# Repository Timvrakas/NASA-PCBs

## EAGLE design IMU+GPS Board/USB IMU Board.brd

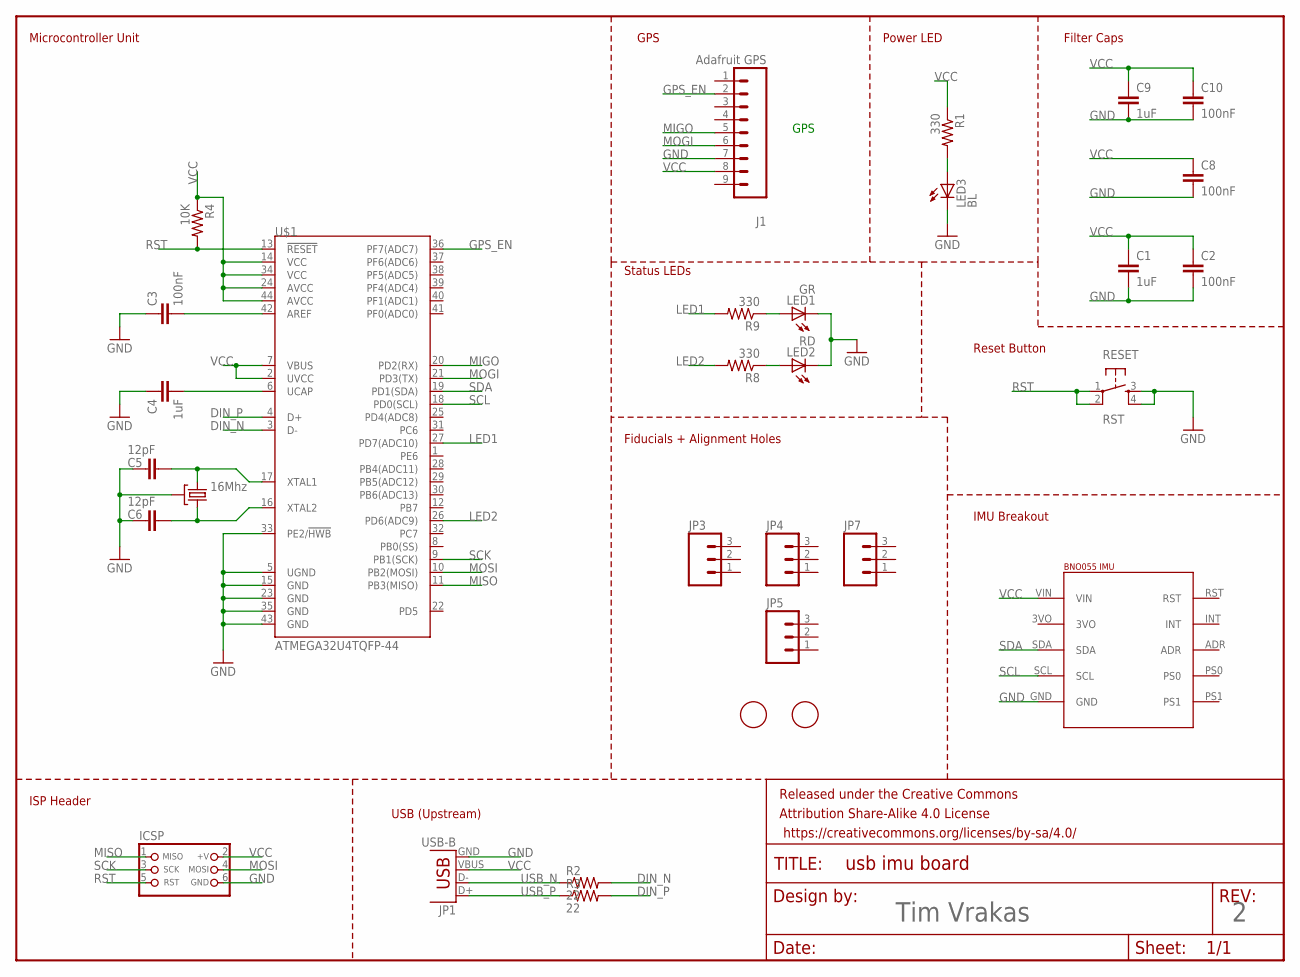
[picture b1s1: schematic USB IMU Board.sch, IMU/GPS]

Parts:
C1, C4, C9: 1uF; 0805
C2, C3, C8, C10: 100nF; 0805
C5, C6: 12pF; 0805
FRAME2: FRAME-LETTERNO_PACKAGE; DUMMY
ICSP: CON_HEADER_PRG_AVR_ICSP-SMD; M2X3_SMD
J1: Adafruit GPS; 1X09
JP1: USB-B; USB-B-PTH
JP3, JP4, JP5, JP7: M03PTH; 1X03
LED1: GR; SML0805
LED2: RD; SML0805
LED3: BL; SML0805
R1, R8, R9: 330; 0805
R2, R3: 22; 0805
R4: 10K; 0805
RESET: RST; TACTILE-SWITCH-SMD
U$1: ATMEGA32U4TQFP-44; TQFP44
U$4: BNO055-IMU; BNO055-BREAKOUT
U$7, U$8: FIDUCIAL; FIDUCIAL_1MM
Y1: 16Mhz; CRYSTAL-SMD-5X3

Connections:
DIN_N: R2.2, U$1.3 (D-)
DIN_P: R3.2, U$1.4 (D+)
GND: C1.2, C2.2, C3.1, C4.1, C5.1, C6.1, C8.2, C9.2, C10.2, ICSP.6 (GND), J1.7, JP1.GND, LED1.C, LED2.C, LED3.C, RESET.3, RESET.4, U$1.5 (UGND), U$1.15 (GND), U$1.23 (GND), U$1.33 (PE2/!HWB), U$1.35 (GND), U$1.43 (GND), U$4.GND, Y1.2 (GND), Y1.4 (GND)
GPS_EN: J1.2, U$1.36 (PF7(ADC7))
LED1: R9.2, U$1.27 (PD7(ADC10))
LED2: R8.2, U$1.26 (PD6(ADC9))
MIGO: J1.5, U$1.20 (PD2(RX))
MISO: ICSP.1 (MISO), U$1.11 (PB3(MISO))
MOGI: J1.6, U$1.21 (PD3(TX))
MOSI: ICSP.4 (MOSI), U$1.10 (PB2(MOSI))
unnamed: C5.2, U$1.17 (XTAL1), Y1.3 (2)
unnamed: C6.2, U$1.16 (XTAL2), Y1.1
unnamed: C3.2, U$1.42 (AREF)
unnamed: LED3.A, R1.2
unnamed: C4.2, U$1.6 (UCAP)
unnamed: LED1.A, R9.1
unnamed: LED2.A, R8.1
RST: ICSP.5 (RST), R4.2, RESET.1, RESET.2, U$1.13 (!RESET)
SCK: ICSP.3 (SCK), U$1.9 (PB1(SCK))
SCL: U$1.18 (PD0(SCL)), U$4.SCL
SDA: U$1.19 (PD1(SDA)), U$4.SDA
USB_N: JP1.D-, R2.1
USB_P: JP1.D+, R3.1
VCC: C1.1, C2.1, C8.1, C9.1, C10.1, ICSP.2 (+V), J1.8, JP1.VBUS, R1.1, R4.1, U$1.2 (UVCC), U$1.7 (VBUS), U$1.14 (VCC), U$1.24 (AVCC), U$1.34 (VCC), U$1.44 (AVCC), U$4.VIN

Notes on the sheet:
IMU Breakout
ISP Header
Microcontroller Unit
GPS
Fiducials + Alignment Holes
Filter Caps
Status LEDs
Power LED
USB (Upstream)
Reset Button

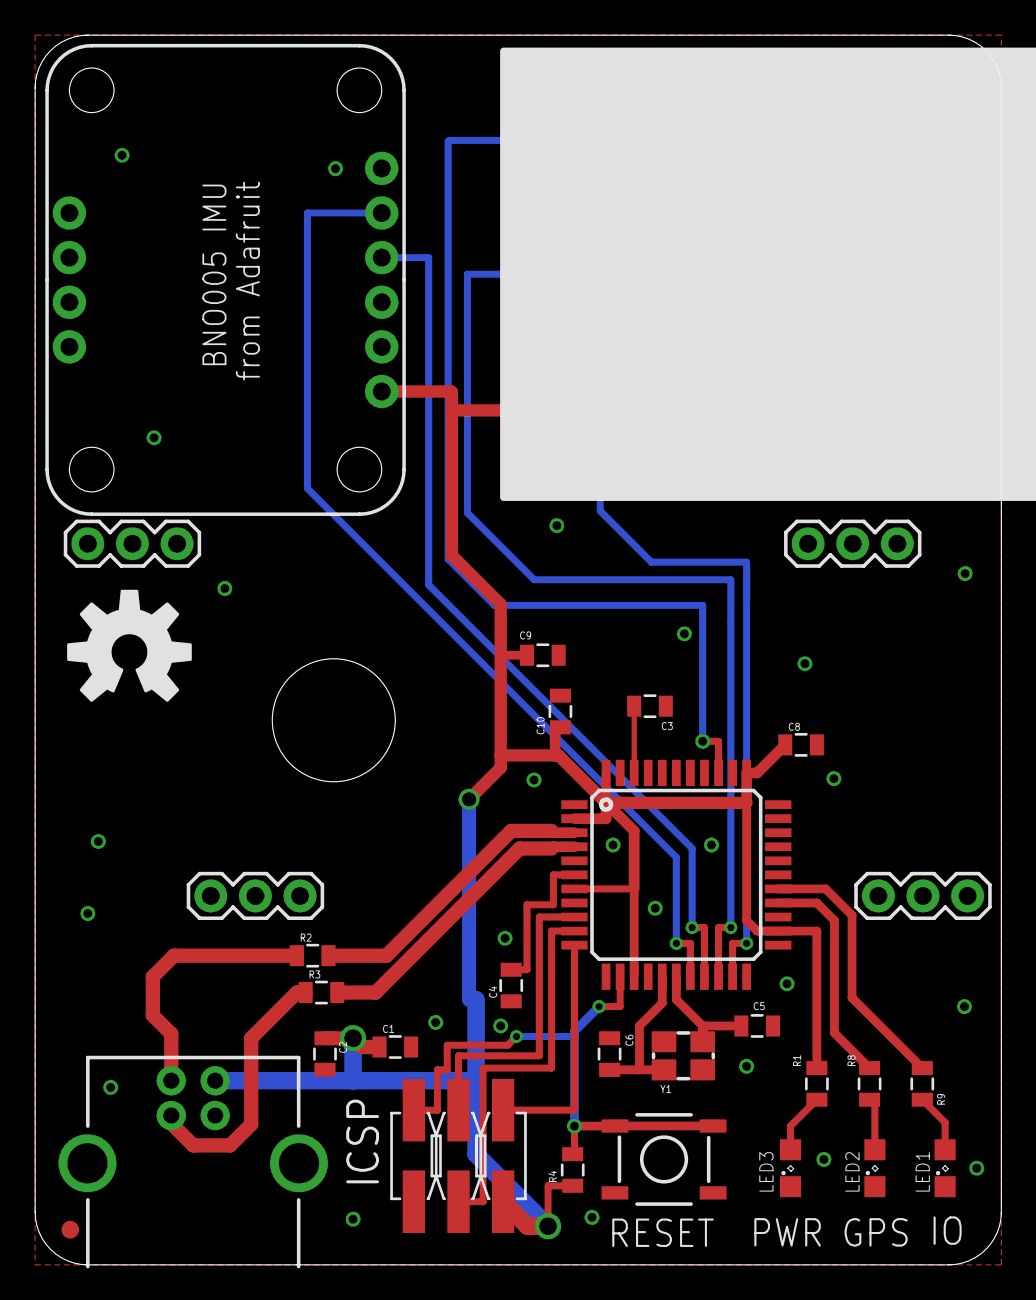
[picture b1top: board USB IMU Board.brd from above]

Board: 2 copper layers, 55.0 x 70.0 mm, 33 parts (0 on the bottom side), 24 nets.

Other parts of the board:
U$9: OSHW-LOGO-L

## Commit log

2015-08-06 Done with schematic (need GPS).
2015-08-15 Finished with Rev.1
    HW Layout done…
2015-08-23 Rev 0.1bc1
    Fixed some things, should be ready
2016-02-28 Tore up USB junk
2016-03-20 First Round of new board
2016-03-31 Rev 0.2bc1 (todo: Hand Review)
2016-06-15 Late Night
    Needs Check
2016-06-15 v3 Board Run
    No going back now!
2016-08-21 USB traces now Impedance Matched
2016-09-02 Version 3b

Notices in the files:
parts and their libraries:
SparkFun-Connectors: Licensing: Creative Commons ShareAlike 4.0 International - https://creativecommons.org/licenses/by-sa/4.0
SparkFun-Aesthetics: Released under the Creative Commons Attribution Share-Alike 4.0 License
SparkFun-Aesthetics: https://creativecommons.org/licenses/by-sa/4.0
